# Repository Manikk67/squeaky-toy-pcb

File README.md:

🧸🔊 Squeaky Toy PCB

A simple **Squeaky Toy PCB** designed as a hands-on project to learn **KiCad** and understand the complete PCB design workflow — from schematic to Gerber files.

---

🎯 Project Purpose
This project was created to **learn KiCad practically** by designing a real, working circuit instead of just doing theory.  
It focuses on schematic design, PCB layout, and manufacturing-ready outputs.

---

⚙️ Circuit Overview
The circuit is based on a **555 Timer IC** configured to drive a buzzer, producing a squeaky sound when powered.

🔩 Main Components
- IC 555
- Resistors
- Capacitors
- Buzzer
- Battery / External power source

---
🔌 Power Specifications
- **Operating Voltage:** 3.3V – 12V  
- **PCB Type:** Single-layer PCB

---

🛠️ Tools Used
- **EDA Tool:** KiCad  
- **Design Time:** ~3 hours

---

📁 Project Contents
- 📐 Schematic (`.kicad_sch`)
- 🧩 PCB Layout (`.kicad_pcb`)
- 🏭 Gerber files (ready for manufacturing)
- 📋 Project configuration files

---

🧠 Learning Outcomes
Through this project, I learned:
- Proper **component placement**
- Efficient **PCB routing**
- Correct **footprint selection**
- Generating **Gerber files** for fabrication
- Understanding the end-to-end PCB design flow

---

🚀 Future Improvements
- Add enclosure-friendly layout
- Optimize trace routing
- Convert to double-layer PCB (advanced version)

---

👤 Author
**MANIKANDAN K**

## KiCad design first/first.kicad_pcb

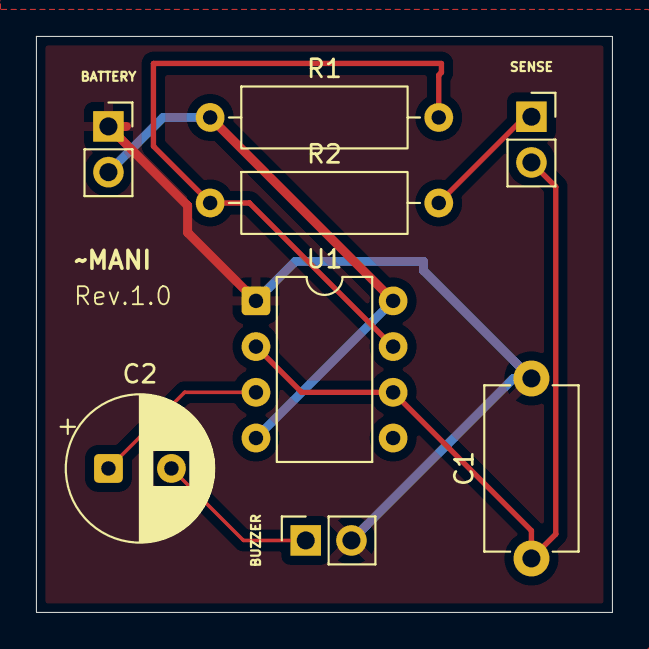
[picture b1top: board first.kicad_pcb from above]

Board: 2 copper layers, 32.0 x 32.0 mm, 8 parts (0 on the bottom side), 7 nets.

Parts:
BATTERY: Battery; PinSocket_1x02_P2.54mm_Vertical
BUZZER: Buzzer; PinSocket_1x02_P2.54mm_Vertical
C1: 1nF; C_Disc_D9.0mm_W5.0mm_P10.00mm
C2: 100uF; CP_Radial_D8.0mm_P3.50mm
R1: 1K; R_Axial_DIN0309_L9.0mm_D3.2mm_P12.70mm_Horizontal
R2: 10K; R_Axial_DIN0309_L9.0mm_D3.2mm_P12.70mm_Horizontal
SENSE: hoomans; PinSocket_1x02_P2.54mm_Vertical
U1: NE555P; DIP-8_W7.62mm

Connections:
/DIS: R1.2, R2.1, U1.7 (DISCH)
/OUT: C2.1, U1.3 (OUT)
/TR: C1.1, SENSE.2, U1.2 (TRIG), U1.6 (THRES)
GND: BATTERY.1, BUZZER.2, C1.2, U1.1 (GND)
unnamed: BUZZER.1, C2.2
unnamed: R2.2, SENSE.1
VCC: BATTERY.2, R1.1, U1.4 (~RST), U1.8 (VCC)

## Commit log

2026-01-10 Revise README to include project overview and details
    Expanded README with project details, components, and learning outcomes.
2026-02-27 Create LICENSE
